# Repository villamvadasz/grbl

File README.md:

# grbl

The Project is not finished yet. Still under work... Lot of the stuffs might be here even outdated.

The Project contains a port of GRBL from Atmel to a PIC32MX and/or PIC32MZ. 
Supposed to run on the boards from Olimex:
- PIC32-RETROBSD (PIC32MX795F512H)
- PIC32-PINGUINO-MICRO
- PIC32-PINGUINO-OTG
- PIC32-HMZ144 @200MHz

As the PIC32-PINGUINO-MICRO, PIC32-PINGUINO-OTG and the PIC32-HMZ144 is out of stock, the project is now running on the PIC32-RETROBSD. Olders boards are still supported but not really tested, or features are turned off (only non-GRBL).
However either a CNC shield is needed or the HW in the hardware section of this project.

The PIC32-HMZ144 is not really tested, but it might compile. Also the bootloader might be outdated.

Features:
- Faster CPU @200MHz/@80MHz -> More CPU time is left for other usefull upcoming features
- More Flash and RAM -> More space for new features
- GRBL code adapted so that much of the synchronous calls are now asynchronous (probe, home, dwell and everything else) -> Easyier integration with other softwarecomponents like FAT32, SPI, AES, USB CDC driver or whatever component that might be used in future.
- Only soft reset is provided, hard reset is removed. -> Sorry but other components might be not happy to be reseted just like so
- Added Eeprom Emulation -> Position save into Data Flash. Since flash is used it only stores changes incrementally, keeps flash long lifed
- USB CDC communication -> No external device is necessary to connect to the PC.
- Ethernet TCP communication
- Unexpected resets now does not lost machine position to an accuracy of +-1 Step
- Bootloader support encrypted files and signature

## Variants
There are no variants now. Former UDP variant is deleted, since it is not really usefull due to lack of transport protocol. USB and Ethernet can work in the same Software together, so there is no need to separate it.

## User Manual
### USB/TCP Ethernet
	Makefile_795F512H
	Makefile_795F512H_simulator
	Makefile_440F256H (for PIC32-PINGUINO-MICRO and Hardware): To build the Real one with a real configuration for the hardware present in the HW section this file is needed
	Makefile_440F256H_simulator (for PIC32-PINGUINO-MICRO and Hardware) : To build a simulator that can be connected and does like a real CNC but does not read in any signals, nor generates them. Ok it is generating them into a dummy variable.
You can connect over Ethernet on Port 5123
	Also availalbe to different CPUs:
	Makefile_460F512L
	Makefile_470F512H 
	Makefile_470F512L
The 200MHz variant is currently under massive rework:
	Makefile_32MZ2048ECG144 (for PIC32-HMZ144): Not working yet.
#### Building the project
Need: XC32 4.20 compiler Full Version.
build_all.bat will build all bootloaders, bootloader updated and application.
build.bat will build application.
#### Flash Bootloader
Need: Mplab 8.92 with PICkit3 (other tools are also good like Mplab X, Mplab IPE, ICD3, ICD4)
The bootloader_PIC project supports builds for USB, ethernet and SDCard, however only one can be active. So when building the project it will emitt different hex file. Currently the USBHIDBootloader_795F512H_RCINT8_F80MHZ_eth_decrypt.hex is used.

* Open the project USBHIDBootloader.mcp. 
* Select debugger tool.
* Optionally change IP address in TCPIPConfig.h. There is no DHCP supported.
* Build or Import one of the prebuilt files. Highly suggested: USBHIDBootloader_795F512H_RCINT8_F80MHZ_eth_decrypt.hex
* Flash.
* Start bootloader_PC. 
* Select USB or Ethernet. 
* Add IP address.
* Connect.
* Add serial number to the label box and click the button. This will write a serial number into the device.
* Add the crypto key to the label box and click the button. This will write a crypto key into the deivce.
#### Bootloader Encryption and Signature
It is highly suggested, that in fazit.txt you add your board. This file is not used activley in any process, but is good for storage.
Format is:
```
Serial number in HEX, Cryptokey for encryption and signature, Not used cryptokey but need to be filled, Some comment for you to know something about the device
```
Here is a simple example for 3 entries:
```
FFFFFFFF FFFFFFFFFFFFFFFFFFFFFFFFFFFFFFFF FFFFFFFFFFFFFFFFFFFFFFFFFFFFFFFF	Empty device
12345678 00112233445566778899AABBCCDDEEFF 4dd63fe3a4e2f099f45f57f8ad3ba5c0	Development 1
DE000001 00112233445566778899AABBCCDDEEFF d24e07819a5901d89dca84de98410cf8	Development 2
```

Before you execute
```
release.bat
```
you must make sure that your device is added there.
```
set FILE_NAME=cnc_1_0_0_795F512H_simulator.hex
set AES_KEY_SIGNATURE=05cf0d46621dc94caac88a97579f2c3f
set AES_KEY_ENCRYPT=15d1b10d061031e25100ffd2ca04e8e8
set AES_KEY_ENCRYPT=%AES_KEY_SIGNATURE%
set SERIAL_NUMBER=DE000003
set BOOTLOADER_UID=NA
call :sign_enc_file_bootloader
```
FILE_NAME: Select also which HEX file to process.

AES_KEY_SIGNATURE: Signature and encryption keys are the same. So you only need to set AES_KEY_SIGNATURE properly. 

SERIAL_NUMBER: This is important since each device have its unique cryptokeys, so this will make sure the output file have a different name.

BOOTLOADER_UID: Must be NA, not used here, only for update over the air (under development).

When done properly, this will take the HEX file specificed, and calculate a signature for it and creates an encrypted one. The encrypted one make sure that a 3rd party can not reverse engineer the file. The signature make sure that only a signed file can be flashed.

Some features are stil missing. Like the same key is used for Encryption and Signature. Also the whole thing might be cryptographically weak. It is more like a demonstration.

#### Flash Application with Encryption
The application must be properly build with build.bat. Make sure that for your device a signature is generated. For this please see the signature chapter.

You need a bootloader that does support encryption on the target! (example: USBHIDBootloader_795F512H_RCINT8_F80MHZ_eth_decrypt.hex)

* Select ENC File for flashing. For example: cnc_1_0_0_795F512H_simulator.hex_DE000003.hex.enc
* Add the signature from the signature_bootloader.txt for the corresponding device and hex file.
* Erase-Program-Verfy
* Run Application
* Disconnect
* Close Bootloader

#### Flash Application without Encryption
The application must be properly build with build.bat.

You need a bootloader that does NOT support encryption on the target! (example: USBHIDBootloader_795F512H_RCINT8_F80MHZ_eth.hex or USBHIDBootloader_795F512H_RCINT8_F80MHZ.hex)

* Select HEX File for flashing. For example: cnc_1_0_0_795F512H_simulator.hex
* Unselect the Enable mark in the Crypto part. This will make sure you are flashing simple hex files.
* Erase-Program-Verfy
* Run Application
* Disconnect
* Close Bootloader

#### UGS
To use the board the UGS is higly suggested:
https://winder.github.io/ugs_website/
	
## Tools
make: Everything is built from build.bat with a make.

bootloader_PC: Bootloader. Can be entered by either doing a Reset or Power On (waits some seconds in the bootloader), or sending BOOTLOADER command in UGS.

netcat: Can be used to send a reset packet. See batch files. Sadly not completly automated. Still need some work, but it works.

disoverer_pc: Sends an UPD broadcast, that will be answered by the device. This way it is earyier to get the IP address.

signer_pc: Used for encryption and signature generation.

eeprom_analyser:

## Configure project
Please see the excel table, which is used to generate the configuration for GRBL.

# Safety Concept
The emergency stop or abort is sensitiv on booth edges (rising and falling). This way, any change on the line will cause an abort. Not only pressing the button, but releasing it too. In case somehow the signal would be inverted, the emergency stop or abort would still work.

The input of the abort is not invertable in SW. It is assumed that:

//uC PIN is 1 ==> Emergency abort button is pressed in, so machine must stop everything

//uC PIN is 0 ==> Emergency abort button is released, it is allowed to move

Stepper enable signal gets disabled after 50ms. This window can be used to slow down the machine (not implemented yet). After 50ms the signal will be set to disable the motors.

Stepper motor enable works only if the function properly calculates some multiplications. This way it must be called with the proper parameter. If by mistake the code is jumped on, there is less likly to enable the stepper motors, since the calculation will fail.

# Note
In some files the Copyright might be deleted by accident. Sorry... But mostly you can assume that either it was the original GRBL author or Microchip.

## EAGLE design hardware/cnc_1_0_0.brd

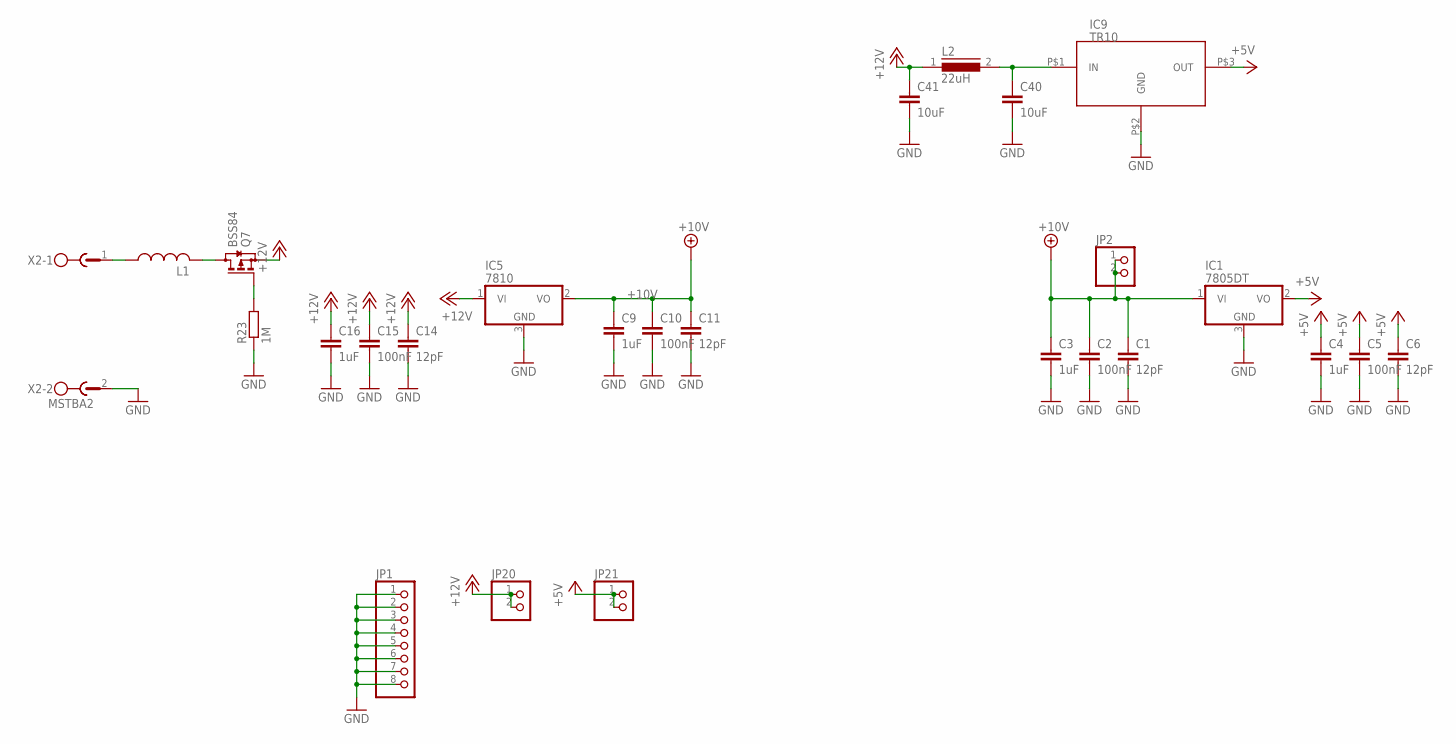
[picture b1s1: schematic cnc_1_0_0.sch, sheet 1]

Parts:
C1, C6, C11, C14: 12pF; C0805K
C2, C5, C10, C15: 100nF; C0805K
C3, C4, C9, C16: 1uF; C0805K
C40, C41: 10uF; C0805K
IC1: 7805DT; TO252
IC5: 7810; TO252
IC9: TR10
JP1: PINHD-1X8; 1X08
JP2, JP20, JP21: PINHD-1X2; 1X02
L1: L-USL1812; L1812
L2: 22uH; DR127
Q7: BSS84; SOT23; FARNELL 1094997
R23: 1M; R0805
X2: MSTBA2

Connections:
+5V: C4.1, C5.1, C6.1, IC1.2 (VO), IC9.P$3 (OUT), JP21.1, JP21.2; also elsewhere on the board
+10V: C1.1, C2.1, C3.1, C9.1, C10.1, C11.1, IC1.1 (VI), IC5.2 (VO), JP2.1, JP2.2; also elsewhere on the board
+12V: C14.1, C15.1, C16.1, C41.1, IC5.1 (VI), JP20.1, JP20.2, L2.1, Q7.2 (S); also elsewhere on the board
GND: C1.2, C2.2, C3.2, C4.2, C5.2, C6.2, C9.2, C10.2, C11.2, C14.2, C15.2, C16.2, C40.2, C41.2, IC1.3 (GND), IC5.3 (GND), IC9.P$2 (GND), JP1.1, JP1.2, JP1.3, JP1.4, JP1.5, JP1.6, JP1.7, JP1.8, R23.1, X2.2; also elsewhere on the board
unnamed: L1.1, X2.1
unnamed: L1.2, Q7.3 (D)
unnamed: Q7.1 (G), R23.2
unnamed: C40.1, IC9.P$1 (IN), L2.2

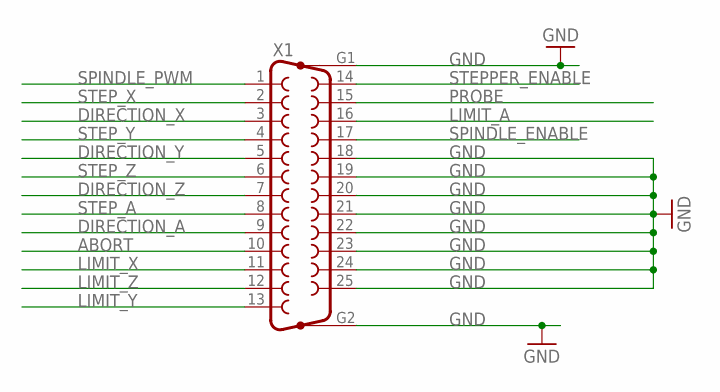
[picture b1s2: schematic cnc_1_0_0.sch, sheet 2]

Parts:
X1: F25HP

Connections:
ABORT: X1.10; also elsewhere on the board
DIRECTION_A: X1.9; also elsewhere on the board
DIRECTION_X: X1.3; also elsewhere on the board
DIRECTION_Y: X1.5; also elsewhere on the board
DIRECTION_Z: X1.7; also elsewhere on the board
GND: X1.18, X1.19, X1.20, X1.21, X1.22, X1.23, X1.24, X1.25, X1.G1, X1.G2; also elsewhere on the board
LIMIT_A: X1.16
LIMIT_X: X1.11; also elsewhere on the board
LIMIT_Y: X1.13; also elsewhere on the board
LIMIT_Z: X1.12; also elsewhere on the board
PROBE: X1.15; also elsewhere on the board
SPINDLE_ENABLE: X1.17; also elsewhere on the board
SPINDLE_PWM: X1.1; also elsewhere on the board
STEPPER_ENABLE: X1.14; also elsewhere on the board
STEP_A: X1.8; also elsewhere on the board
STEP_X: X1.2; also elsewhere on the board
STEP_Y: X1.4; also elsewhere on the board
STEP_Z: X1.6; also elsewhere on the board

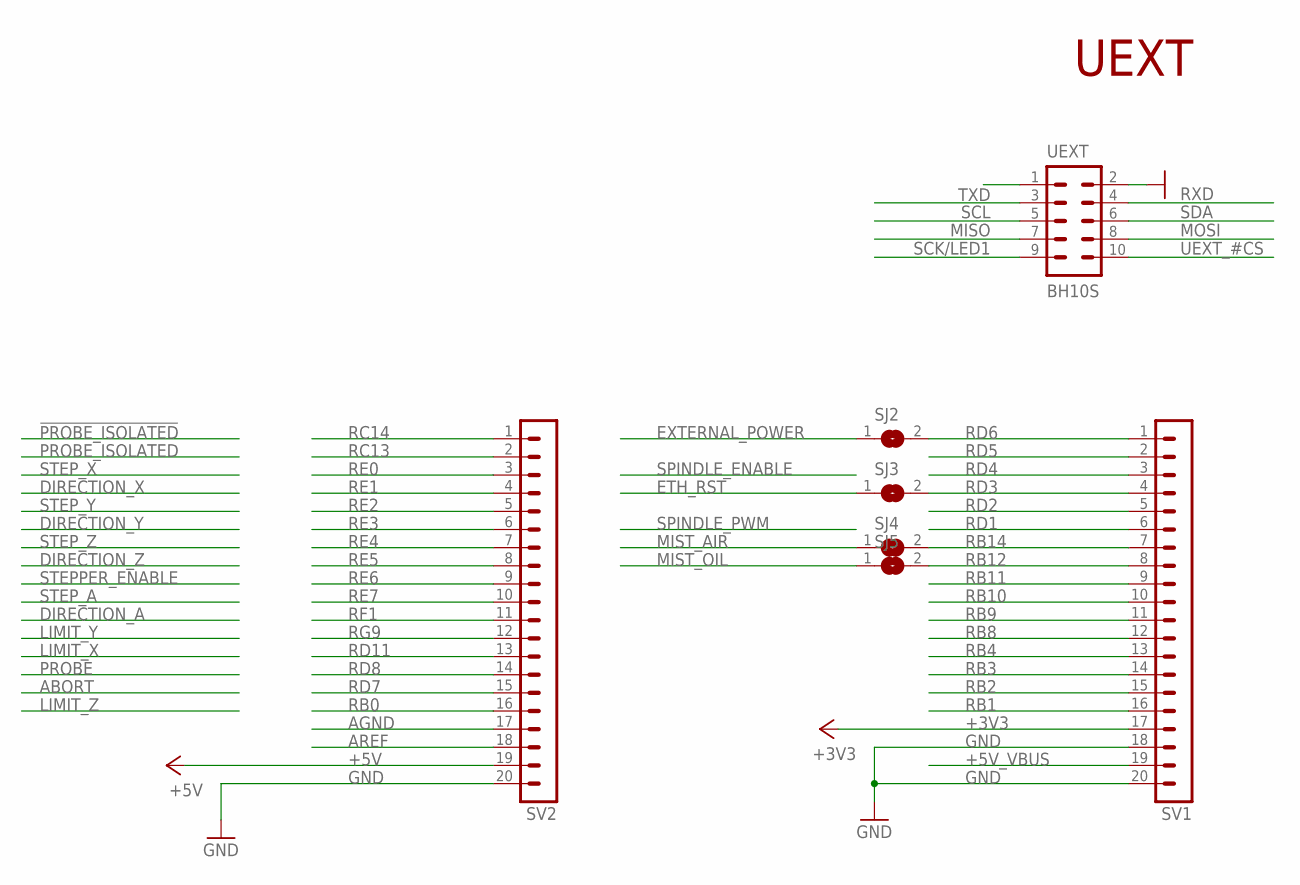
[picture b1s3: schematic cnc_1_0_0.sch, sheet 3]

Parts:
SJ2, SJ3, SJ4, SJ5: SJ
SV1, SV2: MA20-1
UEXT: BH10S; ML10-MALE

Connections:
+3V3: SV1.17; also elsewhere on the board
+5V: SV2.19; also elsewhere on the board
+5V_VBUS: SV1.19
AGND: SV2.17
AREF: SV2.18
ETH_RST: SJ3.1; also elsewhere on the board
EXTERNAL_POWER: SJ2.1; also elsewhere on the board
GND: SV1.18, SV1.20, SV2.20, UEXT.2; also elsewhere on the board
MISO: UEXT.7; also elsewhere on the board
MIST_AIR: SJ4.1; also elsewhere on the board
MIST_OIL: SJ5.1; also elsewhere on the board
MOSI: UEXT.8; also elsewhere on the board
RB0: SV2.16; also elsewhere on the board
RB1: SV1.16
RB2: SV1.15
RB3: SV1.14
RB4: SV1.13
RB8: SV1.12
RB9: SV1.11
RB10: SV1.10
RB11: SV1.9
RB12: SJ5.2, SV1.8
RB14: SJ4.2, SV1.7
RC13: SV2.2; also elsewhere on the board
RC14: SV2.1; also elsewhere on the board
RD1: SV1.6; also elsewhere on the board
RD2: SV1.5
RD3: SJ3.2, SV1.4
RD4: SV1.3; also elsewhere on the board
RD5: SV1.2
RD6: SJ2.2, SV1.1
RD7: SV2.15; also elsewhere on the board
RD8: SV2.14; also elsewhere on the board
RD11: SV2.13; also elsewhere on the board
RE0: SV2.3; also elsewhere on the board
RE1: SV2.4; also elsewhere on the board
RE2: SV2.5; also elsewhere on the board
RE3: SV2.6; also elsewhere on the board
RE4: SV2.7; also elsewhere on the board
RE5: SV2.8; also elsewhere on the board
RE6: SV2.9; also elsewhere on the board
RE7: SV2.10; also elsewhere on the board
RF1: SV2.11; also elsewhere on the board
RG9: SV2.12; also elsewhere on the board
RXD: UEXT.4
SCK/LED1: UEXT.9; also elsewhere on the board
SCL: UEXT.5
SDA: UEXT.6
TXD: UEXT.3
UEXT_#CS: UEXT.10; also elsewhere on the board

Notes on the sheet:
UEXT

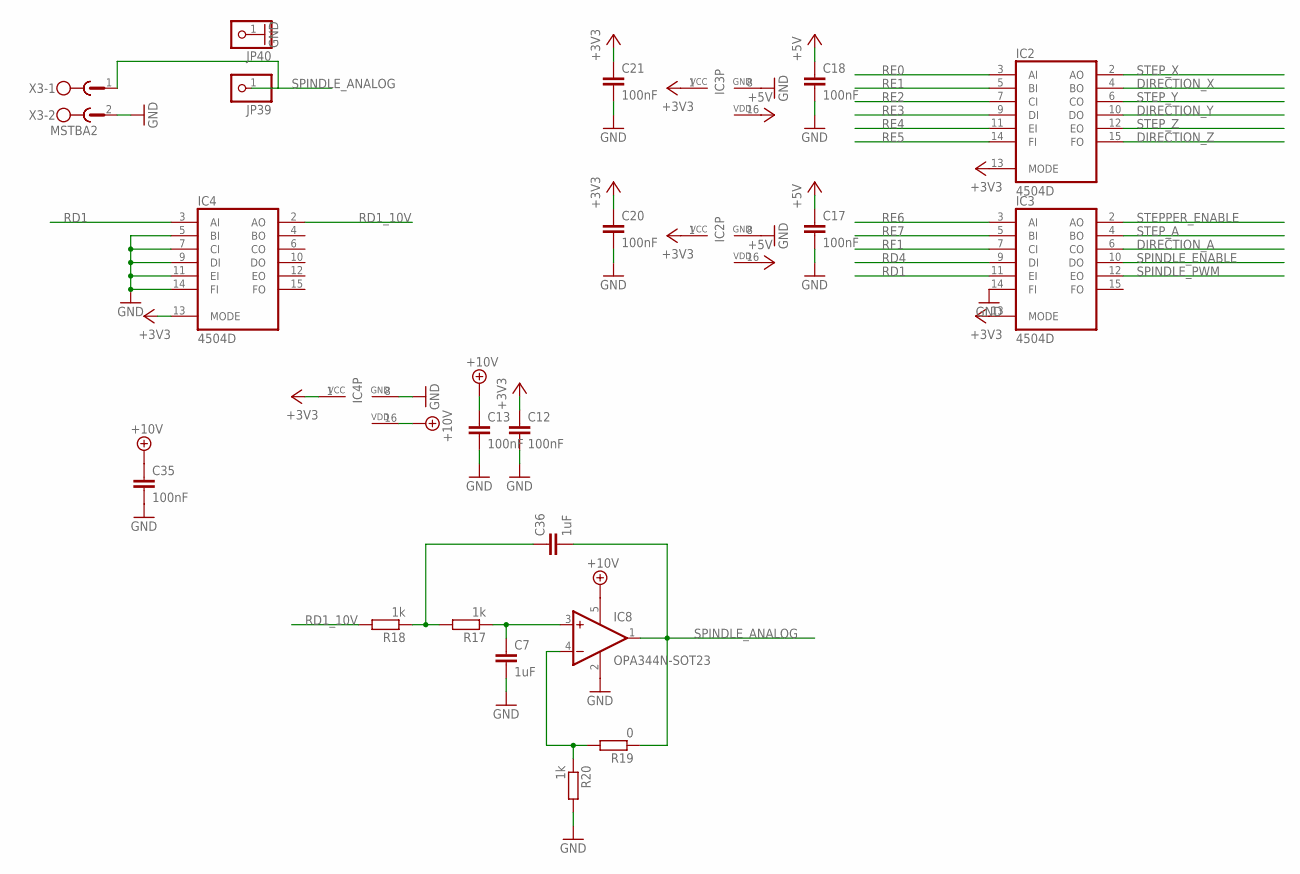
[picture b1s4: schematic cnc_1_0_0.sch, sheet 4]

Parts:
C7, C36: 1uF; C0805K
C12, C13, C17, C18, C20, C21, C35: 100nF; C0805K
IC2, IC3, IC4: 4504D; SO16
IC8: OPA344N-SOT23; SOT23-5
JP39, JP40: PINHD-1X1; 1X01
R17, R18, R20: 1k; R0805
R19: 0; R0805
X3: MSTBA2; MPN 1757242

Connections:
+3V3: C12.1, C20.1, C21.1, IC2.1 (VCC), IC2.13 (MODE), IC3.1 (VCC), IC3.13 (MODE), IC4.1 (VCC), IC4.13 (MODE); also elsewhere on the board
+5V: C17.1, C18.1, IC2.16 (VDD), IC3.16 (VDD); also elsewhere on the board
+10V: C13.1, C35.1, IC4.16 (VDD), IC8.5 (V+); also elsewhere on the board
DIRECTION_A: IC3.6 (CO); also elsewhere on the board
DIRECTION_X: IC2.4 (BO); also elsewhere on the board
DIRECTION_Y: IC2.10 (DO); also elsewhere on the board
DIRECTION_Z: IC2.15 (FO); also elsewhere on the board
GND: C7.2, C12.2, C13.2, C17.2, C18.2, C20.2, C21.2, C35.2, IC2.8 (GND), IC3.8 (GND), IC3.14 (FI), IC4.5 (BI), IC4.7 (CI), IC4.8 (GND), IC4.9 (DI), IC4.11 (EI), IC4.14 (FI), IC8.2 (V-), JP40.1, R20.2, X3.2; also elsewhere on the board
unnamed: C36.1, R17.2, R18.1
unnamed: C7.1, IC8.3 (+IN), R17.1
unnamed: IC8.4 (-IN), R19.2, R20.1
RD1: IC3.11 (EI), IC4.3 (AI); also elsewhere on the board
RD1_10V: IC4.2 (AO), R18.2
RD4: IC3.9 (DI); also elsewhere on the board
RE0: IC2.3 (AI); also elsewhere on the board
RE1: IC2.5 (BI); also elsewhere on the board
RE2: IC2.7 (CI); also elsewhere on the board
RE3: IC2.9 (DI); also elsewhere on the board
RE4: IC2.11 (EI); also elsewhere on the board
RE5: IC2.14 (FI); also elsewhere on the board
RE6: IC3.3 (AI); also elsewhere on the board
RE7: IC3.5 (BI); also elsewhere on the board
RF1: IC3.7 (CI); also elsewhere on the board
SPINDLE_ANALOG: C36.2, IC8.1 (OUT), JP39.1, R19.1, X3.1
SPINDLE_ENABLE: IC3.10 (DO); also elsewhere on the board
SPINDLE_PWM: IC3.12 (EO); also elsewhere on the board
STEPPER_ENABLE: IC3.2 (AO); also elsewhere on the board
STEP_A: IC3.4 (BO); also elsewhere on the board
STEP_X: IC2.2 (AO); also elsewhere on the board
STEP_Y: IC2.6 (CO); also elsewhere on the board
STEP_Z: IC2.12 (EO); also elsewhere on the board

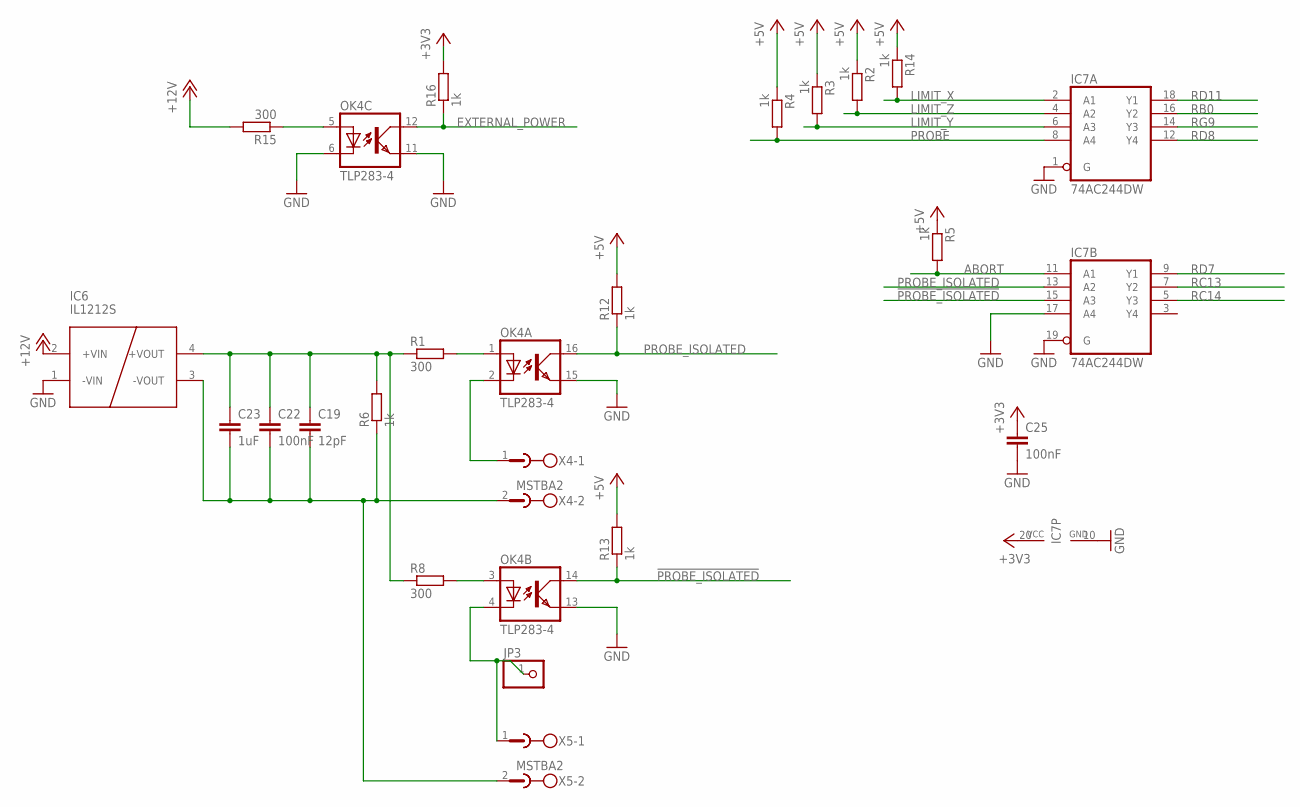
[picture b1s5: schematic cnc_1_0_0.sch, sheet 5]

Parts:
C19: 12pF; C0805K
C22, C25: 100nF; C0805K
C23: 1uF; C0805K
IC6: IL1212S; SIL4
IC7: 74AC244DW; SO20W
JP3: PINHD-1X1; 1X01
OK4: TLP283-4; MINI-FLAT-16
R1, R8, R15: 300; R0805
R2, R3, R4, R5, R6, R12, R13, R14, R16: 1k; R0805
X4: MSTBA2; MPN 1757242
X5: MSTBA2

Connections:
!PROBE_ISOLATED: IC7.15 (A3), OK4.14 (COL), R13.1
+3V3: C25.1, IC7.20 (VCC), R16.2; also elsewhere on the board
+5V: R2.1, R3.1, R4.1, R5.1, R12.2, R13.2, R14.1; also elsewhere on the board
+10V1: C19.1, C22.1, C23.1, IC6.4 (+VOUT), R1.1, R6.2, R8.1
+12V: IC6.2 (+VIN), R15.2; also elsewhere on the board
ABORT: IC7.11 (A1), R5.2; also elsewhere on the board
EXTERNAL_POWER: OK4.12 (COL), R16.1; also elsewhere on the board
GND: C25.2, IC6.1 (-VIN), IC7.1 (G), IC7.10 (GND), IC7.17 (A4), IC7.19 (G), OK4.6 (C), OK4.11 (EMIT), OK4.13 (EMIT), OK4.15 (EMIT); also elsewhere on the board
LIMIT_X: IC7.2 (A1), R14.2; also elsewhere on the board
LIMIT_Y: IC7.6 (A3), R3.2; also elsewhere on the board
LIMIT_Z: IC7.4 (A2), R2.2; also elsewhere on the board
unnamed: OK4.1 (A), R1.2
unnamed: OK4.2 (C), X4.1
unnamed: C19.2, C22.2, C23.2, IC6.3 (-VOUT), R6.1, X4.2, X5.2
unnamed: OK4.3 (A), R8.2
unnamed: JP3.1, OK4.4 (C), X5.1
unnamed: OK4.5 (A), R15.1
PROBE: IC7.8 (A4), R4.2; also elsewhere on the board
PROBE_ISOLATED: IC7.13 (A2), OK4.16 (COL), R12.1
RB0: IC7.16 (Y2); also elsewhere on the board
RC13: IC7.7 (Y2); also elsewhere on the board
RC14: IC7.5 (Y3); also elsewhere on the board
RD7: IC7.9 (Y1); also elsewhere on the board
RD8: IC7.12 (Y4); also elsewhere on the board
RD11: IC7.18 (Y1); also elsewhere on the board
RG9: IC7.14 (Y3); also elsewhere on the board

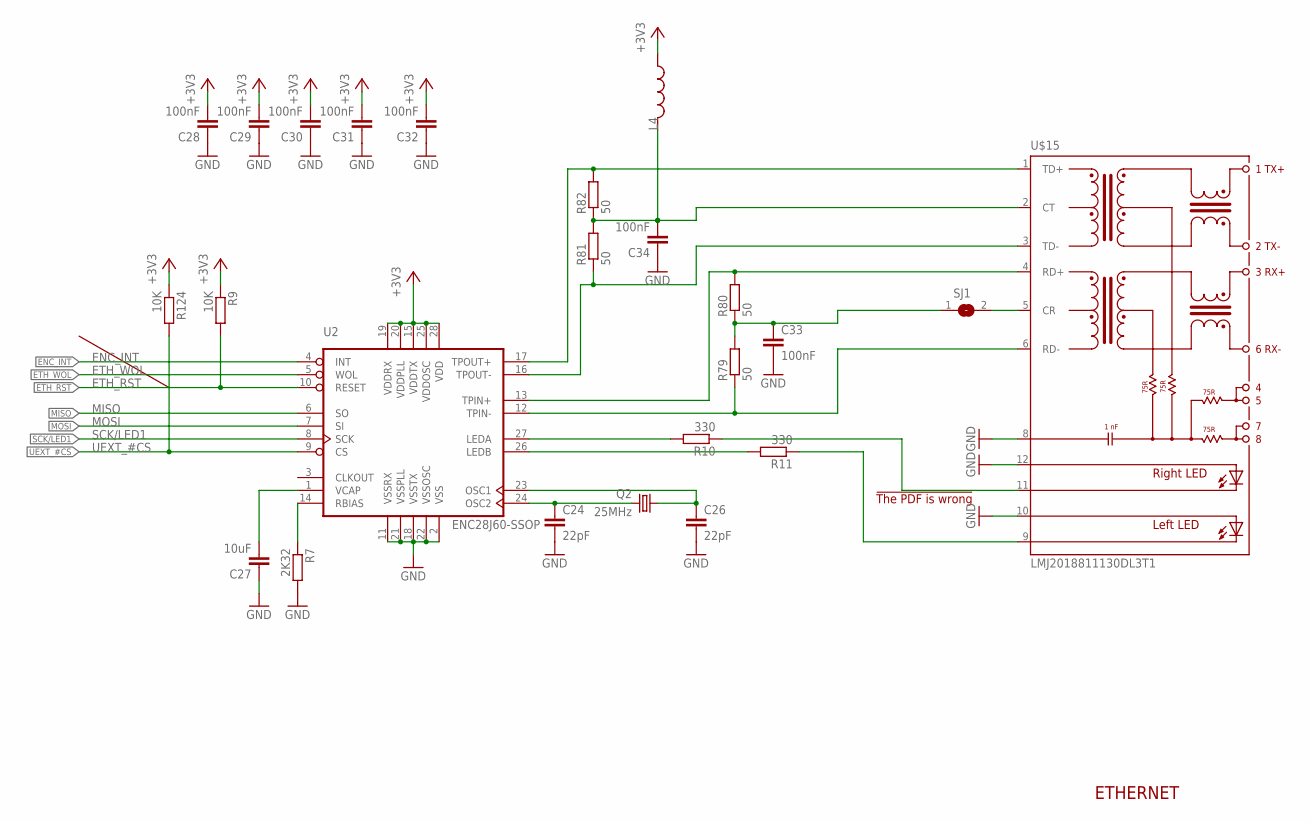
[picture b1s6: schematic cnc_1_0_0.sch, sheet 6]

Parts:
C24, C26: 22pF; C0603
C27: 10uF; C0805K
C28, C29, C30, C31, C32, C33, C34: 100nF; C0603
L4: INDUCTOR0603; 0603
Q2: 25MHz; CRYSTAL-SMD-5X3
R7: 2K32; R0805
R9, R124: 10K; R0805
R10, R11: 330; R0805
R79, R80, R81, R82: 50; R0603
SJ1: SJ
U2: ENC28J60-SSOP; SSOP28
U$15: LMJ2018811130DL3T1; AMPHENOL-LMJ2018814100DL2T1B_RJ45

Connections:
+3V3: C28.2, C29.2, C30.2, C31.2, C32.2, L4.1, R9.1, R124.1, U2.15 (VDDTX), U2.19 (VDDRX), U2.20 (VDDPLL), U2.25 (VDDOSC), U2.28 (VDD); also elsewhere on the board
CT1: C34.2, L4.2, R81.2, R82.1, U$15.2 (CT)
ENC_INT: U2.4 (INT)
ETH_RST: R9.2, U2.10 (RESET); also elsewhere on the board
ETH_WOL: U2.5 (WOL)
GND: C24.2, C26.2, C27.1, C28.1, C29.1, C30.1, C31.1, C32.1, C33.2, C34.1, R7.2, U2.2 (VSS), U2.11 (VSSRX), U2.18 (VSSTX), U2.21 (VSSPLL), U2.22 (VSSOSC), U$15.8, U$15.10 (A-L), U$15.12 (A-R); also elsewhere on the board
MISO: U2.6 (SO); also elsewhere on the board
MOSI: U2.7 (SI); also elsewhere on the board
unnamed: C24.1, Q2.3 (2), U2.24 (OSC2)
unnamed: R11.2, U2.26 (LEDB)
unnamed: SJ1.2, U$15.5 (CR)
unnamed: R10.2, U2.27 (LEDA)
unnamed: C26.1, Q2.1, U2.23 (OSC1)
unnamed: R7.1, U2.14 (RBIAS)
unnamed: C27.2, U2.1 (VCAP)
unnamed: C33.1, R79.2, R80.1, SJ1.1
unnamed: R10.1, U$15.11 (C-R)
unnamed: R11.1, U$15.9 (C-L)
SCK/LED1: U2.8 (SCK); also elsewhere on the board
TPIN+: R80.2, U2.13 (TPIN+), U$15.4 (RD+)
TPIN-: R79.1, U2.12 (TPIN-), U$15.6 (RD-)
TPOUT+: R82.2, U2.17 (TPOUT+), U$15.1 (TD+)
TPOUT-: R81.1, U2.16 (TPOUT-), U$15.3 (TD-)
UEXT_#CS: R124.2, U2.9 (CS); also elsewhere on the board

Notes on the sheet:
ETHERNET
!The PDF is wrong!

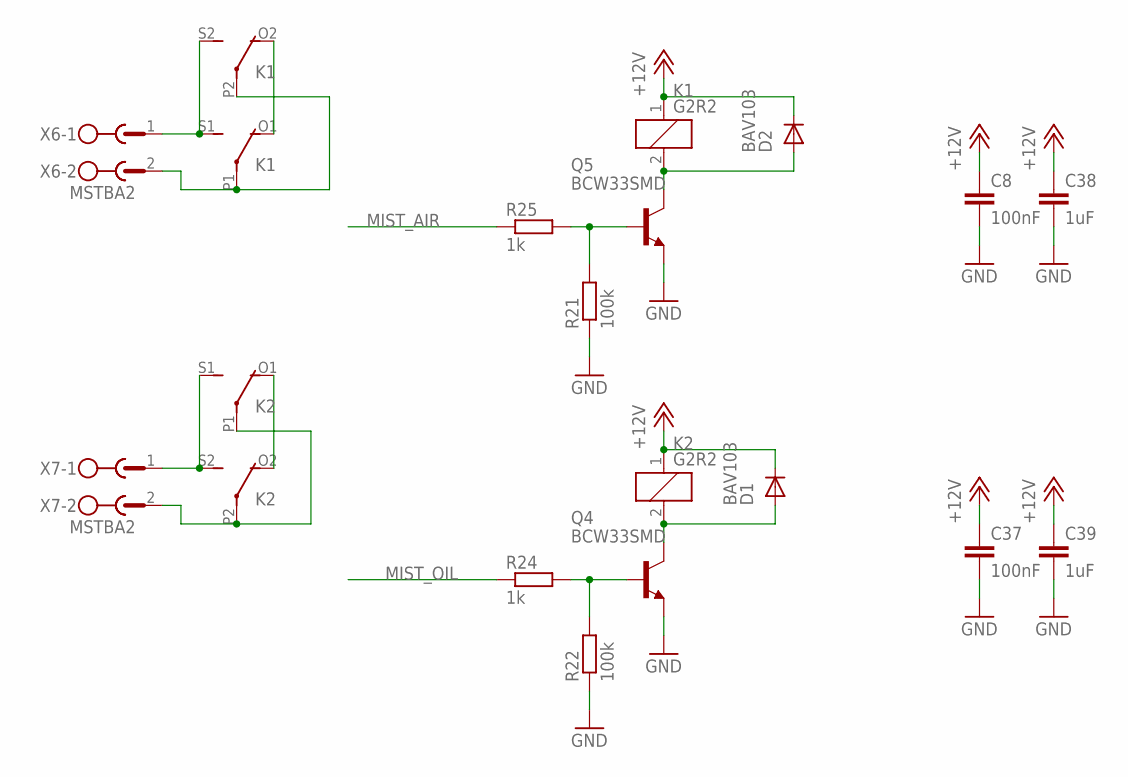
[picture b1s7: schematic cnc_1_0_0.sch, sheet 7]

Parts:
C8, C37: 100nF; C0805K
C38, C39: 1uF; C0805K
D1, D2: BAV103; MINIMELF
K1, K2: G2R2; MPN G2R-2-DC6
Q4, Q5: BCW33SMD; SOT23-BEC
R21, R22: 100k; R0805
R24, R25: 1k; R0805
X6, X7: MSTBA2; MPN 1757242

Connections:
+12V: C8.1, C37.1, C38.1, C39.1, D1.C, D2.C, K1.1, K2.1; also elsewhere on the board
GND: C8.2, C37.2, C38.2, C39.2, Q4.E, Q5.E, R21.1, R22.1; also elsewhere on the board
MIST_AIR: R25.1; also elsewhere on the board
MIST_OIL: R24.1; also elsewhere on the board
unnamed: K2.S1 (S), K2.S2 (S), X7.1
unnamed: K2.O1 (O), K2.O2 (O)
unnamed: K2.P1, K2.P2, X7.2
unnamed: K1.P1, K1.P2, X6.2
unnamed: K1.O1 (O), K1.O2 (O)
unnamed: K1.S1 (S), K1.S2 (S), X6.1
unnamed: D2.A, K1.2, Q5.C
unnamed: D1.A, K2.2, Q4.C
unnamed: Q4.B, R22.2, R24.2
unnamed: Q5.B, R21.2, R25.2

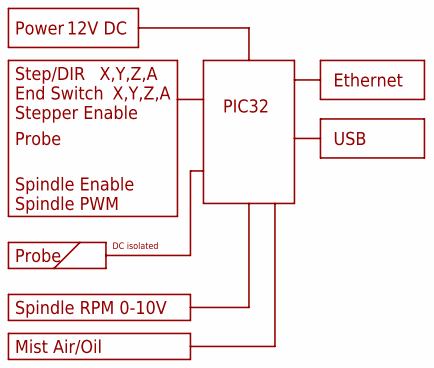
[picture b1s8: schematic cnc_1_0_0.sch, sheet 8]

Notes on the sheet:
PIC32
Ethernet
USB
Step/DIR
Probe
X,Y,Z,A
End Switch
Power
12V DC
Spindle Enable
Spindle PWM
Spindle RPM 0-10V
Stepper Enable
DC isolated
Mist Air/Oil

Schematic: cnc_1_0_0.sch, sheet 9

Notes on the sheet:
GND
LIMIT X
LIMIT Y
LIMIT Z
Lookin in front out of the box

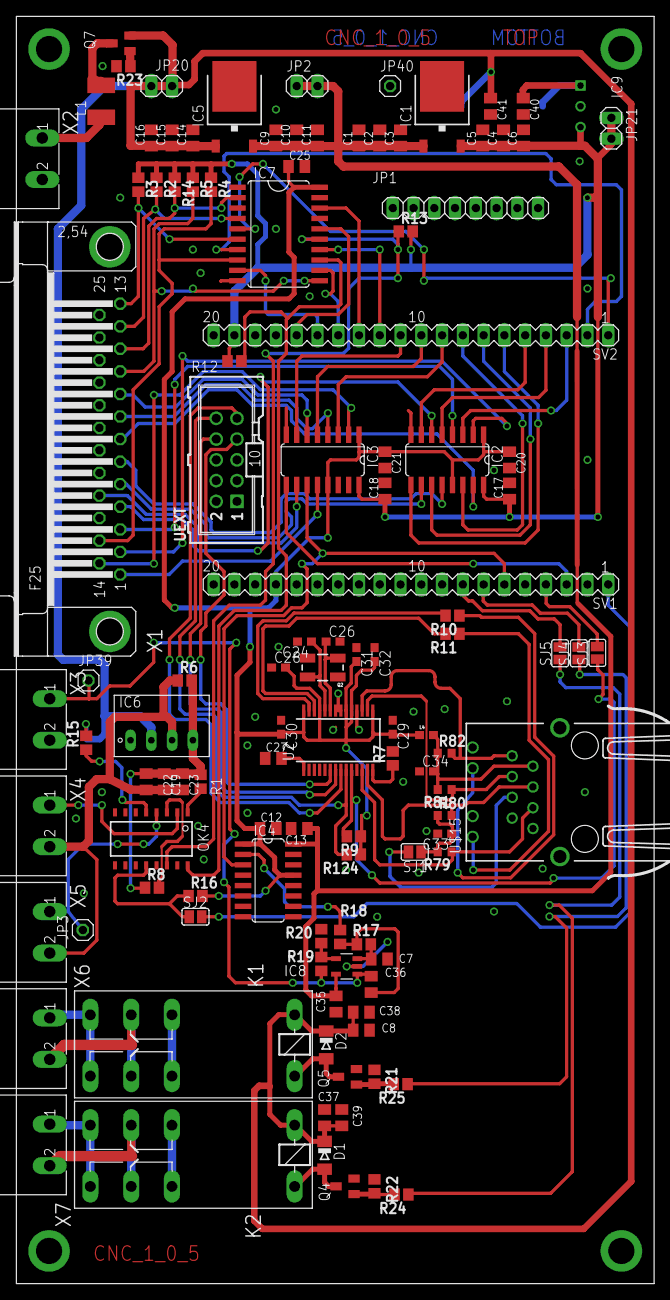
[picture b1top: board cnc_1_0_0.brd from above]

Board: 2 copper layers, 78.0 x 155.0 mm, 116 parts (1 on the bottom side), 94 nets.

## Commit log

2020-04-17 Updated text.
2020-04-17 Initial import of Ethernet and USB project.
2020-04-17 Recompiled. Updatd text.
2020-04-17 Moved files.
2020-04-17 Add Hardware files for USB variant.
2021-01-23 Update.
2021-02-03 Fixed problem with abort input. It was not working at all :(
2021-02-21 Small Update.
2021-02-21 Deleted file because windows 10 always throws a warning about it.
2021-02-21 Recompiled.
2024-01-20 Lot of changes. Sorry no real commit message here.
2025-12-13 Lot of changes. Sorry no real commit message here. Deleted file because windows 10 always throws a warning about it. Small Update. Fixed problem with abort input. It was not working at all :( Add Har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
2025-12-13 Updated to new version. Still in development.
